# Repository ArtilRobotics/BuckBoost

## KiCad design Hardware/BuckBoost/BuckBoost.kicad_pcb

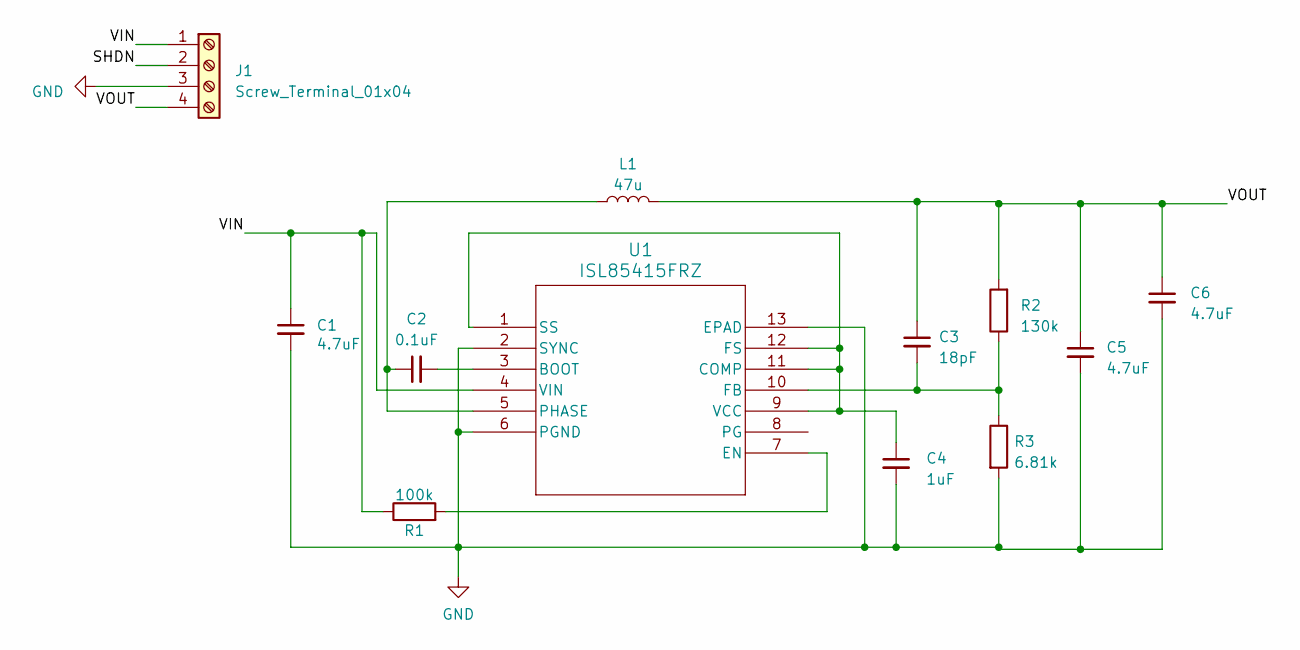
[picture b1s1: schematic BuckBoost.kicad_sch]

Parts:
C1, C5, C6: 4.7uF_1206_lowESR; C_1206; Part Number EMF316AB7475KLHT
C2: 100nF_0603_16V; CP_Elec_5x5.3; Part Number 0603YC104KAT2A; JLCPCB ID C14663
C3: 18pF_0603_50V; CP_Elec_5x5.3; Part Number C0603C180J5GACTU; JLCPCB ID C1647
C4: 1uF_0603_25V; C_0603; Part Number GRM188R61E105KA12D; JLCPCB ID C15849
J1: Screw_Terminal_01x04; TerminalBlock_Phoenix_PT-1,5-4-3.5-H_1x04_P3.50mm_Horizontal
L1: 47u; IND_TYS4012100M-10
R1: 100k_0603; R_0603; Part Number RC0603FR-07100KL; JLCPCB ID C25803
R2: 130k; R_0603; Part Number RC0603FR-07100KL; JLCPCB ID C25803
R3: 6.81k; R_0603; Part Number RC0603FR-07100KL; JLCPCB ID C25803
U1: ISL85415FRZ; DFN12_4X3_INR

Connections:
/SHDN: J1.2
/VIN: C1.1, J1.1, R1.1, U1.4 (VIN)
/VOUT: C3.1, C5.1, C6.1, J1.4, L1.2, R2.2
GND: C1.2, C4.2, C5.2, C6.2, J1.3, R3.2, U1.2 (SYNC), U1.6 (PGND), U1.13 (EPAD)
unnamed: C2.2, U1.3 (BOOT)
unnamed: C4.1, U1.1 (SS), U1.9 (VCC), U1.11 (COMP), U1.12 (FS)
unnamed: R1.2, U1.7 (EN)
unnamed: C3.2, R2.1, R3.1, U1.10 (FB)
unnamed: C2.1, L1.1, U1.5 (PHASE)

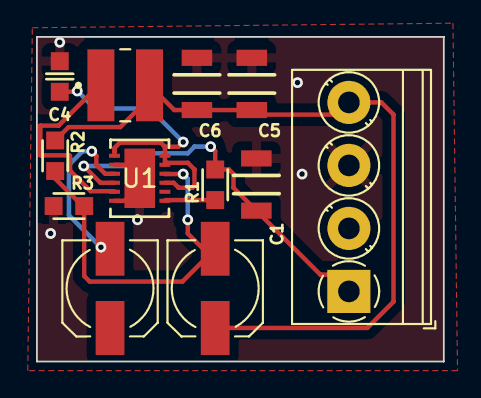
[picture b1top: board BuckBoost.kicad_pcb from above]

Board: 2 copper layers, 22.6 x 18.0 mm, 12 parts (0 on the bottom side), 8 nets.

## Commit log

2023-06-21 Feat: Added PCB and update schematic
2023-06-22 doc: simulaciones
2023-07-06 feat: Update PCB
